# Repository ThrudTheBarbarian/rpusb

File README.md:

# rpusb
USB hub connecting RP2040s

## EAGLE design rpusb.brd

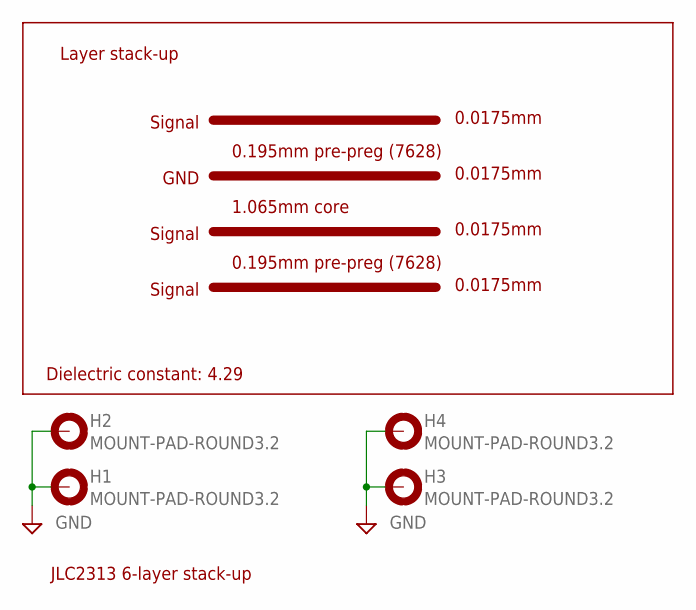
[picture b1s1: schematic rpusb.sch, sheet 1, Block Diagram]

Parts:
H1, H2, H3, H4: MOUNT-PAD-ROUND3.2; 3,2-PAD

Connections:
GND: H1.B3,2, H2.B3,2, H3.B3,2, H4.B3,2; also elsewhere on the board

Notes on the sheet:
JLC2313 6-layer stack-up
0.0175mm
Layer stack-up
Dielectric constant: 4.29
Signal
GND
0.195mm pre-preg (7628)
1.065mm core

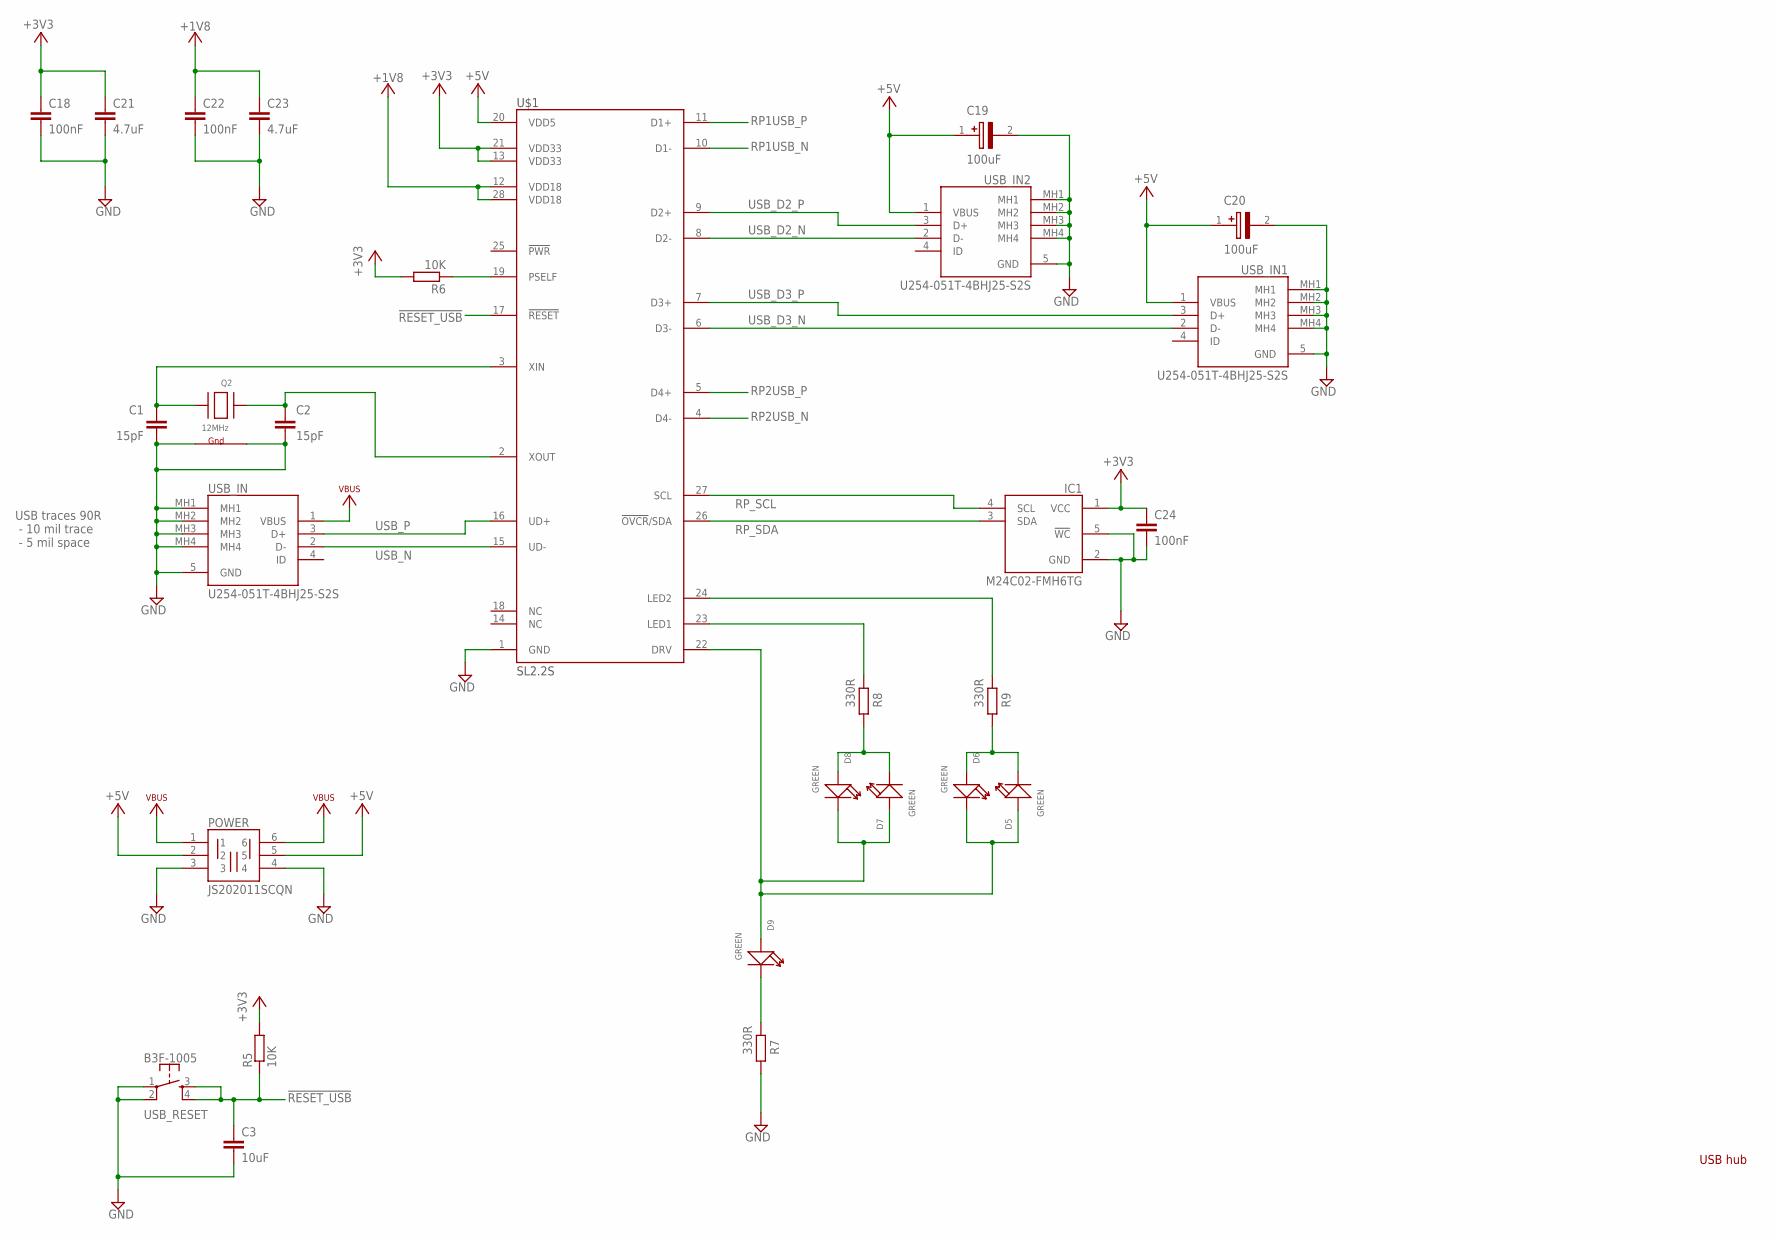
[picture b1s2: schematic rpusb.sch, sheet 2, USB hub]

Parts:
C1, C2: 15pF; C0201
C3: 10uF; C0402
C18, C22, C24: 100nF; C0201
C19, C20: 100uF; CAPAE530X550N
C21, C23: 4.7uF; C0402
D5, D6, D7, D8, D9: GREEN; LED-0603
IC1: M24C02-FMH6TG; M24C32FMH6TG
POWER: JS202011SCQN
Q2: 12MHz; NX3225
R5, R6: 10K; R0201
R7, R8, R9: 330R; R0201
U$1: SL2.2S; SSOP28-0.635
USB_IN, USB_IN1, USB_IN2: U254-051T-4BHJ25-S2S; U254051T4BHJ25S2S
USB_RESET: B3F-1005; TACTILE-PTH

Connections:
!RESET_USB!: C3.1, R5.1, U$1.17 (!RESET!), USB_RESET.3, USB_RESET.4
+1V8: C22.1, C23.1, U$1.12 (VDD18), U$1.28 (VDD18)
+3V3: C18.1, C21.1, C24.1, IC1.1 (VCC), R5.2, R6.2, U$1.13 (VDD33), U$1.21 (VDD33)
+5V: C19.1 (+), C20.1 (+), POWER.2, POWER.5, U$1.20 (VDD5), USB_IN1.1 (VBUS), USB_IN2.1 (VBUS); also elsewhere on the board
GND: C1.2, C2.2, C3.2, C18.2, C19.2 (-), C20.2 (-), C21.2, C22.2, C23.2, C24.2, IC1.2 (GND), IC1.5 (!WC), POWER.3, POWER.4, Q2.2 (G2), Q2.4 (G1), R7.1, U$1.1 (GND), USB_IN.5 (GND), USB_IN.MH1, USB_IN.MH2, USB_IN.MH3, USB_IN.MH4, USB_IN1.5 (GND), USB_IN1.MH1, USB_IN1.MH2, USB_IN1.MH3, USB_IN1.MH4, USB_IN2.5 (GND), USB_IN2.MH1, USB_IN2.MH2, USB_IN2.MH3, USB_IN2.MH4, USB_RESET.1, USB_RESET.2; also elsewhere on the board
unnamed: D9.-, R7.2
unnamed: C2.1, Q2.3 (X2), U$1.2 (XOUT)
unnamed: R6.1, U$1.19 (PSELF)
unnamed: C1.1, Q2.1 (X1), U$1.3 (XIN)
unnamed: R8.2, U$1.23 (LED1)
unnamed: D7.-, D8.+, R8.1
unnamed: D5.+, D6.-, D7.+, D8.-, D9.+, U$1.22 (DRV)
unnamed: R9.2, U$1.24 (LED2)
unnamed: D5.-, D6.+, R9.1
RP1USB_N: U$1.10 (D1-); also elsewhere on the board
RP1USB_P: U$1.11 (D1+); also elsewhere on the board
RP2USB_N: U$1.4 (D4-); also elsewhere on the board
RP2USB_P: U$1.5 (D4+); also elsewhere on the board
RP_SCL: IC1.4 (SCL), U$1.27 (SCL); also elsewhere on the board
RP_SDA: IC1.3 (SDA), U$1.26 (!OVCR!/SDA); also elsewhere on the board
USB_D2_N: U$1.8 (D2-), USB_IN2.2 (D-)
USB_D2_P: U$1.9 (D2+), USB_IN2.3 (D+)
USB_D3_N: U$1.6 (D3-), USB_IN1.2 (D-)
USB_D3_P: U$1.7 (D3+), USB_IN1.3 (D+)
USB_N: U$1.15 (UD-), USB_IN.2 (D-)
USB_P: U$1.16 (UD+), USB_IN.3 (D+)
VBUS: POWER.1, POWER.6, USB_IN.1 (VBUS); also elsewhere on the board

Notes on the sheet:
USB hub
USB traces 90R - 10 mil trace - 5 mil space

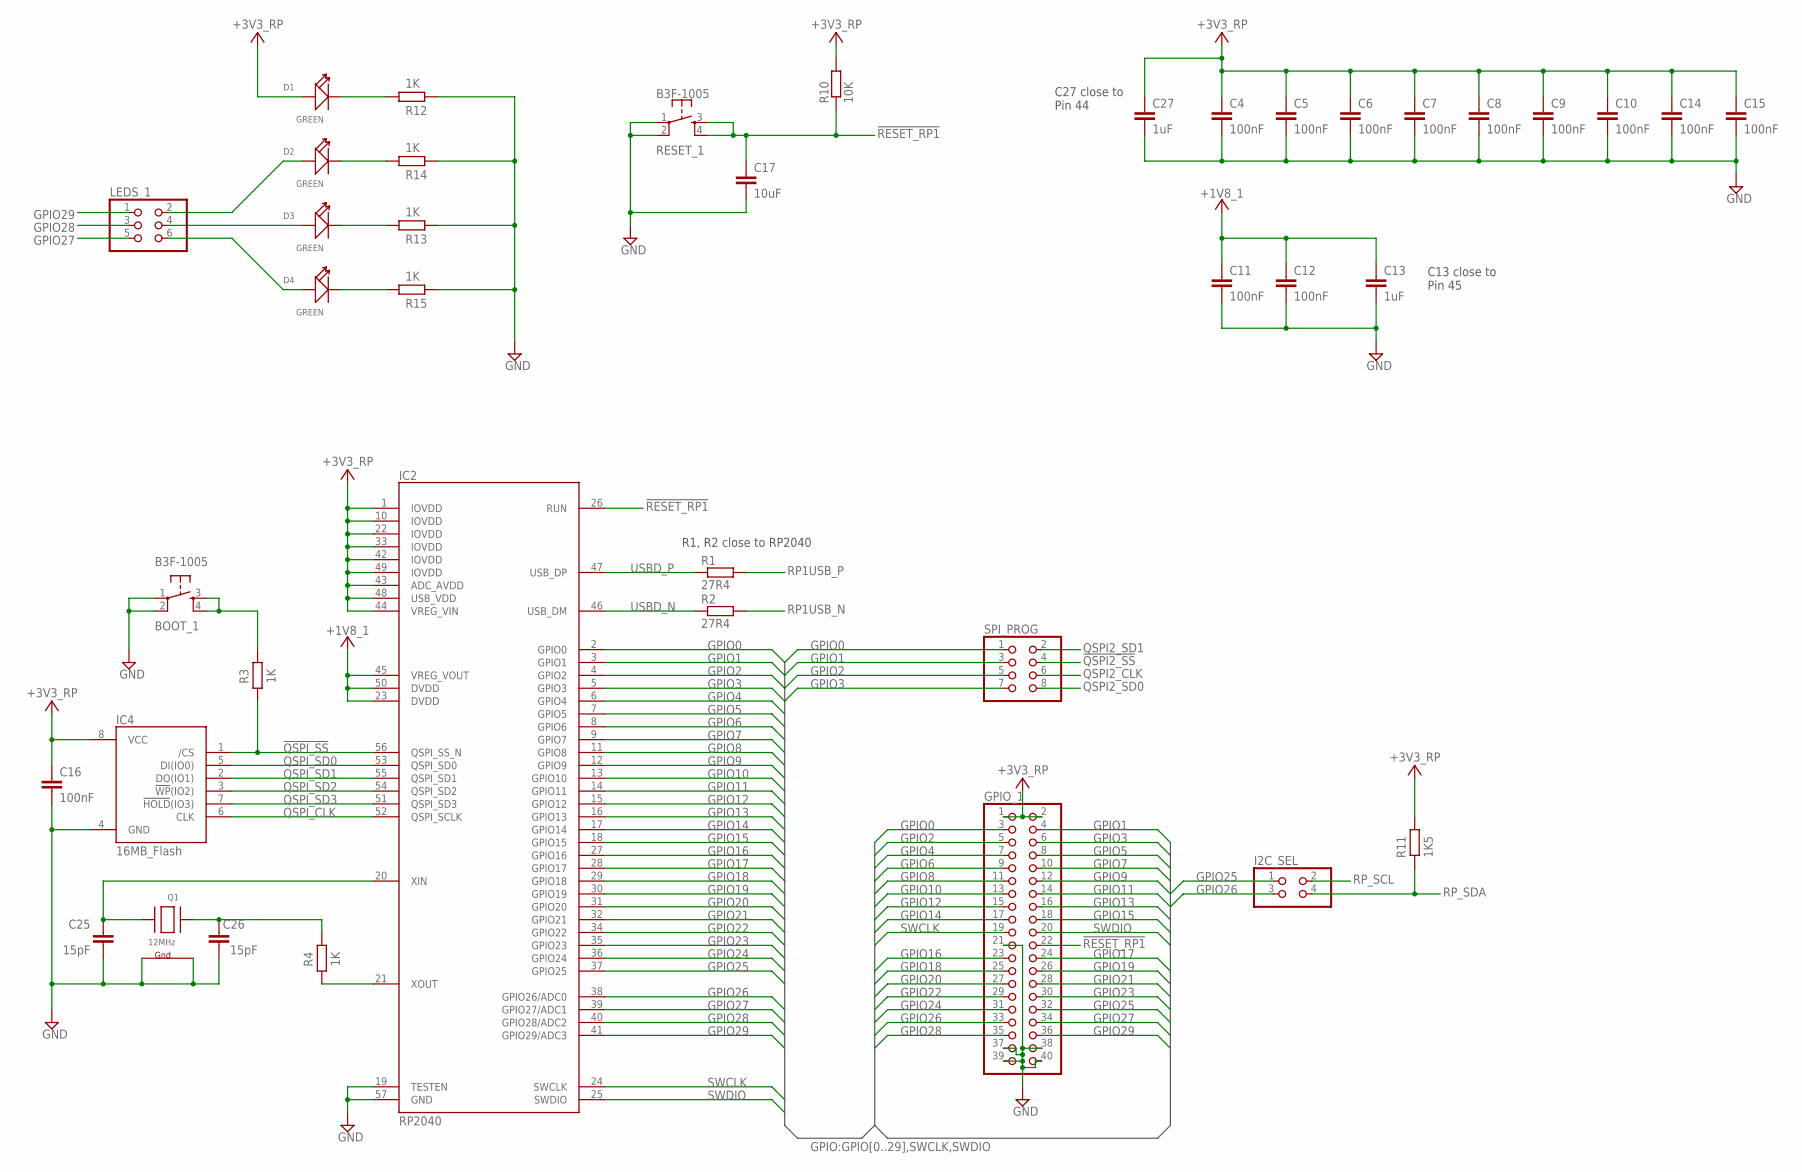
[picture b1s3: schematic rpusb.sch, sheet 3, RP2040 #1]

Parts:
BOOT_1: B3F-1005; TACTILE-PTH
C4, C5, C6, C7, C8, C9, C10, C11, C12, C14, C15, C16: 100nF; C0201
C13, C27: 1uF; C0201
C17: 10uF; C0402
C25, C26: 15pF; C0201
D1, D2, D3, D4: GREEN; LED-0603
GPIO_1: PINHD-2X20; 2X20
I2C_SEL: PINHD-2X2; 2X02
IC2: RP2040; QFN40P700X700X90-57N
IC4: 16MB_Flash; SOIC127P790X216-8N
LEDS_1: PINHD-2X3; 2X03
Q1: 12MHz; NX3225
R1, R2: 27R4; R0201
R3, R4, R12, R13, R14, R15: 1K; R0201
R10: 10K; R0201
R11: 1K5; R0201
RESET_1: B3F-1005; TACTILE-PTH
SPI_PROG: PINHD-2X4; 2X04

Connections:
!QSPI2_SS!: SPI_PROG.4; also elsewhere on the board
!QSPI_SS!: IC2.56 (QSPI_SS_N), IC4.1 (/CS), R3.2
!RESET_RP1!: C17.1, GPIO_1.22, IC2.26 (RUN), R10.1, RESET_1.3, RESET_1.4
+1V8_1: C11.1, C12.1, C13.1, IC2.23 (DVDD), IC2.45 (VREG_VOUT), IC2.50 (DVDD)
+3V3_RP: C4.1, C5.1, C6.1, C7.1, C8.1, C9.1, C10.1, C14.1, C15.1, C16.1, C27.1, D1.+, GPIO_1.1, GPIO_1.2, IC2.1 (IOVDD), IC2.10 (IOVDD), IC2.22 (IOVDD), IC2.33 (IOVDD), IC2.42 (IOVDD), IC2.43 (ADC_AVDD), IC2.44 (VREG_VIN), IC2.48 (USB_VDD), IC2.49 (IOVDD), IC4.8 (VCC), R10.2, R11.1; also elsewhere on the board
GND: BOOT_1.1, BOOT_1.2, C4.2, C5.2, C6.2, C7.2, C8.2, C9.2, C10.2, C11.2, C12.2, C13.2, C14.2, C15.2, C16.2, C17.2, C25.2, C26.2, C27.2, GPIO_1.21, GPIO_1.37, GPIO_1.38, GPIO_1.39, GPIO_1.40, IC2.19 (TESTEN), IC2.57 (GND), IC4.4 (GND), Q1.2 (G2), Q1.4 (G1), R12.2, R13.2, R14.2, R15.2, RESET_1.1, RESET_1.2; also elsewhere on the board
GPIO0: GPIO_1.3, IC2.2 (GPIO0), SPI_PROG.1
GPIO1: GPIO_1.4, IC2.3 (GPIO1), SPI_PROG.3
GPIO2: GPIO_1.5, IC2.4 (GPIO2), SPI_PROG.5
GPIO3: GPIO_1.6, IC2.5 (GPIO3), SPI_PROG.7
GPIO4: GPIO_1.7, IC2.6 (GPIO4)
GPIO5: GPIO_1.8, IC2.7 (GPIO5)
GPIO6: GPIO_1.9, IC2.8 (GPIO6)
GPIO7: GPIO_1.10, IC2.9 (GPIO7)
GPIO8: GPIO_1.11, IC2.11 (GPIO8)
GPIO9: GPIO_1.12, IC2.12 (GPIO9)
GPIO10: GPIO_1.13, IC2.13 (GPIO10)
GPIO11: GPIO_1.14, IC2.14 (GPIO11)
GPIO12: GPIO_1.15, IC2.15 (GPIO12)
GPIO13: GPIO_1.16, IC2.16 (GPIO13)
GPIO14: GPIO_1.17, IC2.17 (GPIO14)
GPIO15: GPIO_1.18, IC2.18 (GPIO15)
GPIO16: GPIO_1.23, IC2.27 (GPIO16)
GPIO17: GPIO_1.24, IC2.28 (GPIO17)
GPIO18: GPIO_1.25, IC2.29 (GPIO18)
GPIO19: GPIO_1.26, IC2.30 (GPIO19)
GPIO20: GPIO_1.27, IC2.31 (GPIO20)
GPIO21: GPIO_1.28, IC2.32 (GPIO21)
GPIO22: GPIO_1.29, IC2.34 (GPIO22)
GPIO23: GPIO_1.30, IC2.35 (GPIO23)
GPIO24: GPIO_1.31, IC2.36 (GPIO24)
GPIO25: GPIO_1.32, I2C_SEL.1, IC2.37 (GPIO25)
GPIO26: GPIO_1.33, I2C_SEL.3, IC2.38 (GPIO26/ADC0)
GPIO27: GPIO_1.34, IC2.39 (GPIO27/ADC1), LEDS_1.5
GPIO28: GPIO_1.35, IC2.40 (GPIO28/ADC2), LEDS_1.3
GPIO29: GPIO_1.36, IC2.41 (GPIO29/ADC3), LEDS_1.1
unnamed: D1.-, R12.1
unnamed: D2.-, R14.1
unnamed: BOOT_1.3, BOOT_1.4, R3.1
unnamed: D3.-, R13.1
unnamed: IC2.21 (XOUT), R4.2
unnamed: D4.-, R15.1
unnamed: D2.+, LEDS_1.2
unnamed: D3.+, LEDS_1.4
unnamed: D4.+, LEDS_1.6
unnamed: C26.1, Q1.3 (X2), R4.1
unnamed: C25.1, IC2.20 (XIN), Q1.1 (X1)
QSPI2_CLK: SPI_PROG.6; also elsewhere on the board
QSPI2_SD0: SPI_PROG.8; also elsewhere on the board
QSPI2_SD1: SPI_PROG.2; also elsewhere on the board
QSPI_CLK: IC2.52 (QSPI_SCLK), IC4.6 (CLK)
QSPI_SD0: IC2.53 (QSPI_SD0), IC4.5 (DI(IO0))
QSPI_SD1: IC2.55 (QSPI_SD1), IC4.2 (DO(IO1))
QSPI_SD2: IC2.54 (QSPI_SD2), IC4.3 (!WP!(IO2))
QSPI_SD3: IC2.51 (QSPI_SD3), IC4.7 (!HOLD!(IO3))
RP1USB_N: R2.2; also elsewhere on the board
RP1USB_P: R1.2; also elsewhere on the board
RP_SCL: I2C_SEL.2; also elsewhere on the board
RP_SDA: I2C_SEL.4, R11.2; also elsewhere on the board
SWCLK: GPIO_1.19, IC2.24 (SWCLK)
SWDIO: GPIO_1.20, IC2.25 (SWDIO)
USBD_N: IC2.46 (USB_DM), R2.1
USBD_P: IC2.47 (USB_DP), R1.1

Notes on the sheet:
R1, R2 close to RP2040
C13 close to Pin 45
C27 close to Pin 44

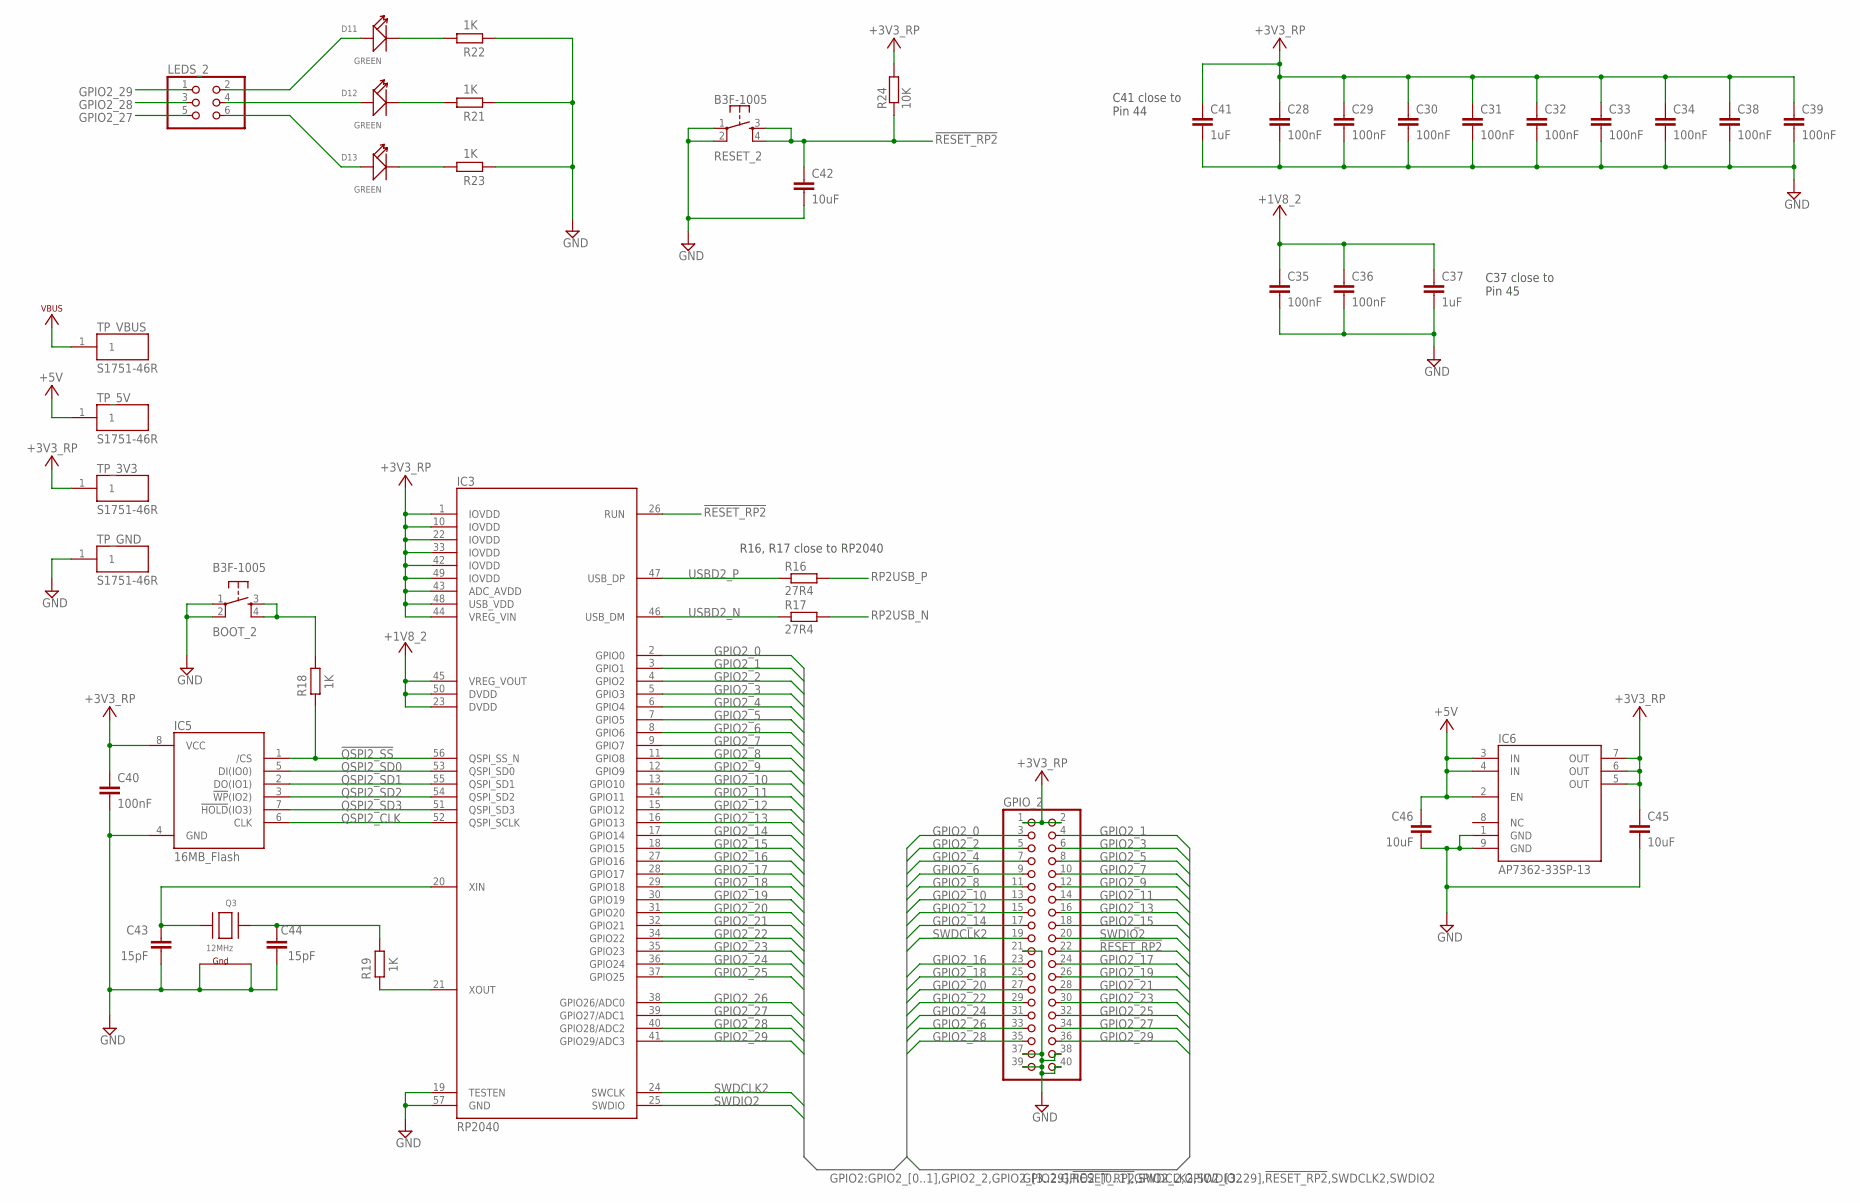
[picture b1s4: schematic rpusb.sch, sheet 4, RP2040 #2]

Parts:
BOOT_2: B3F-1005; TACTILE-PTH
C28, C29, C30, C31, C32, C33, C34, C35, C36, C38, C39, C40: 100nF; C0201
C37, C41: 1uF; C0201
C42, C45, C46: 10uF; C0402
C43, C44: 15pF; C0201
D11, D12, D13: GREEN; LED-0603
GPIO_2: PINHD-2X20; 2X20
IC3: RP2040; QFN40P700X700X90-57N
IC5: 16MB_Flash; SOIC127P790X216-8N
IC6: AP7362-33SP-13; SOIC127P600X163-9N
LEDS_2: PINHD-2X3; 2X03
Q3: 12MHz; NX3225
R16, R17: 27R4; R0201
R18, R19, R21, R22, R23: 1K; R0201
R24: 10K; R0201
RESET_2: B3F-1005; TACTILE-PTH
TP_3V3, TP_5V: S1751-46R; S175146R
TP_GND: S1751-46R; S175146R
TP_VBUS: S1751-46R; S175146R

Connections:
!QSPI2_SS!: IC3.56 (QSPI_SS_N), IC5.1 (/CS), R18.2; also elsewhere on the board
!RESET_RP2!: C42.1, GPIO_2.22, IC3.26 (RUN), R24.1, RESET_2.3, RESET_2.4
+1V8_2: C35.1, C36.1, C37.1, IC3.23 (DVDD), IC3.45 (VREG_VOUT), IC3.50 (DVDD)
+3V3_RP: C28.1, C29.1, C30.1, C31.1, C32.1, C33.1, C34.1, C38.1, C39.1, C40.1, C41.1, C45.1, GPIO_2.1, GPIO_2.2, IC3.1 (IOVDD), IC3.10 (IOVDD), IC3.22 (IOVDD), IC3.33 (IOVDD), IC3.42 (IOVDD), IC3.43 (ADC_AVDD), IC3.44 (VREG_VIN), IC3.48 (USB_VDD), IC3.49 (IOVDD), IC5.8 (VCC), IC6.5 (OUT), IC6.6 (OUT), IC6.7 (OUT), R24.2, TP_3V3.1; also elsewhere on the board
+5V: C46.1, IC6.2 (EN), IC6.3 (IN), IC6.4 (IN), TP_5V.1; also elsewhere on the board
GND: BOOT_2.1, BOOT_2.2, C28.2, C29.2, C30.2, C31.2, C32.2, C33.2, C34.2, C35.2, C36.2, C37.2, C38.2, C39.2, C40.2, C41.2, C42.2, C43.2, C44.2, C45.2, C46.2, GPIO_2.21, GPIO_2.37, GPIO_2.38, GPIO_2.39, GPIO_2.40, IC3.19 (TESTEN), IC3.57 (GND), IC5.4 (GND), IC6.1 (GND), IC6.9 (GND), Q3.2 (G2), Q3.4 (G1), R21.2, R22.2, R23.2, RESET_2.1, RESET_2.2, TP_GND.1; also elsewhere on the board
GPIO2_0: GPIO_2.3, IC3.2 (GPIO0)
GPIO2_1: GPIO_2.4, IC3.3 (GPIO1)
GPIO2_2: GPIO_2.5, IC3.4 (GPIO2)
GPIO2_3: GPIO_2.6, IC3.5 (GPIO3)
GPIO2_4: GPIO_2.7, IC3.6 (GPIO4)
GPIO2_5: GPIO_2.8, IC3.7 (GPIO5)
GPIO2_6: GPIO_2.9, IC3.8 (GPIO6)
GPIO2_7: GPIO_2.10, IC3.9 (GPIO7)
GPIO2_8: GPIO_2.11, IC3.11 (GPIO8)
GPIO2_9: GPIO_2.12, IC3.12 (GPIO9)
GPIO2_10: GPIO_2.13, IC3.13 (GPIO10)
GPIO2_11: GPIO_2.14, IC3.14 (GPIO11)
GPIO2_12: GPIO_2.15, IC3.15 (GPIO12)
GPIO2_13: GPIO_2.16, IC3.16 (GPIO13)
GPIO2_14: GPIO_2.17, IC3.17 (GPIO14)
GPIO2_15: GPIO_2.18, IC3.18 (GPIO15)
GPIO2_16: GPIO_2.23, IC3.27 (GPIO16)
GPIO2_17: GPIO_2.24, IC3.28 (GPIO17)
GPIO2_18: GPIO_2.25, IC3.29 (GPIO18)
GPIO2_19: GPIO_2.26, IC3.30 (GPIO19)
GPIO2_20: GPIO_2.27, IC3.31 (GPIO20)
GPIO2_21: GPIO_2.28, IC3.32 (GPIO21)
GPIO2_22: GPIO_2.29, IC3.34 (GPIO22)
GPIO2_23: GPIO_2.30, IC3.35 (GPIO23)
GPIO2_24: GPIO_2.31, IC3.36 (GPIO24)
GPIO2_25: GPIO_2.32, IC3.37 (GPIO25)
GPIO2_26: GPIO_2.33, IC3.38 (GPIO26/ADC0)
GPIO2_27: GPIO_2.34, IC3.39 (GPIO27/ADC1), LEDS_2.5
GPIO2_28: GPIO_2.35, IC3.40 (GPIO28/ADC2), LEDS_2.3
GPIO2_29: GPIO_2.36, IC3.41 (GPIO29/ADC3), LEDS_2.1
unnamed: BOOT_2.3, BOOT_2.4, R18.1
unnamed: IC3.21 (XOUT), R19.2
unnamed: D11.-, R22.1
unnamed: D12.-, R21.1
unnamed: D13.-, R23.1
unnamed: D11.+, LEDS_2.2
unnamed: D12.+, LEDS_2.4
unnamed: D13.+, LEDS_2.6
unnamed: C44.1, Q3.3 (X2), R19.1
unnamed: C43.1, IC3.20 (XIN), Q3.1 (X1)
QSPI2_CLK: IC3.52 (QSPI_SCLK), IC5.6 (CLK); also elsewhere on the board
QSPI2_SD0: IC3.53 (QSPI_SD0), IC5.5 (DI(IO0)); also elsewhere on the board
QSPI2_SD1: IC3.55 (QSPI_SD1), IC5.2 (DO(IO1)); also elsewhere on the board
QSPI2_SD2: IC3.54 (QSPI_SD2), IC5.3 (!WP!(IO2))
QSPI2_SD3: IC3.51 (QSPI_SD3), IC5.7 (!HOLD!(IO3))
RP2USB_N: R17.2; also elsewhere on the board
RP2USB_P: R16.2; also elsewhere on the board
SWDCLK2: GPIO_2.19, IC3.24 (SWCLK)
SWDIO2: GPIO_2.20, IC3.25 (SWDIO)
USBD2_N: IC3.46 (USB_DM), R17.1
USBD2_P: IC3.47 (USB_DP), R16.1
VBUS: TP_VBUS.1; also elsewhere on the board

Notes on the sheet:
R16, R17 close to RP2040
C37 close to Pin 45
C41 close to Pin 44

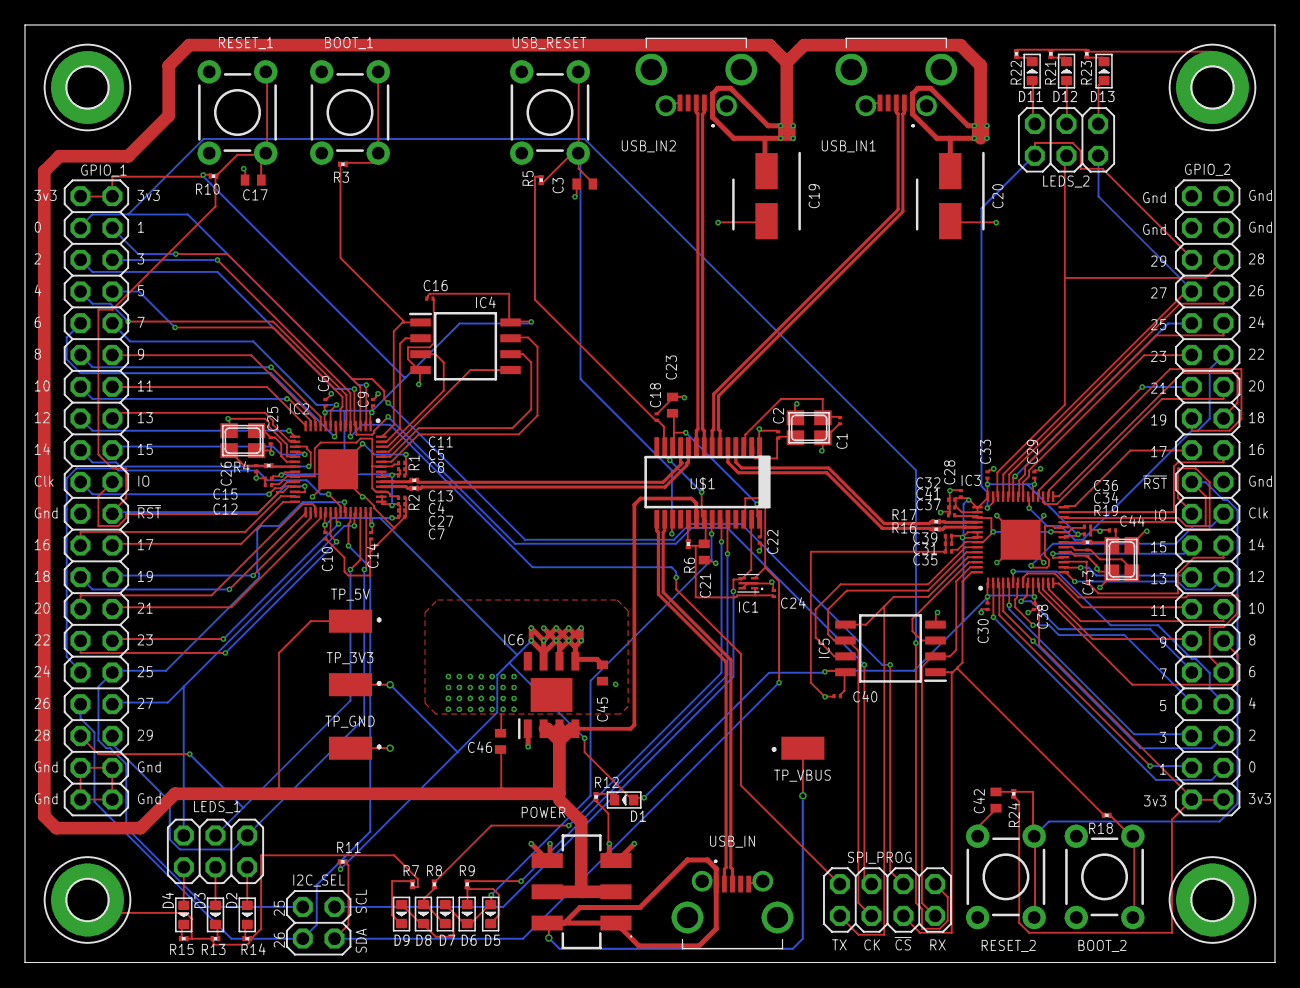
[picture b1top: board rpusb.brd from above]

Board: 4 copper layers, 100.0 x 75.0 mm, 114 parts (0 on the bottom side), 133 nets.

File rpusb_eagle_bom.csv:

"Qty";"Value";"Device";"Package";"Parts";"Description";"ARROW_PART_NUMBER";"ARROW_PRICE-STOCK";"DESCRIPTION";"HEIGHT";"MANUFACTURER_NAME";"MANUFACTURER_PART_NUMBER";"MOUSER_PART_NUMBER";"MOUSER_PRICE-STOCK";"MPN";"POPULARITY";"SPICEPREFIX";"USE";"VALUE";
"1";"";"PINHD-2X2";"2X02";"I2C_SEL";"PIN HEADER";"";"";"";"";"";"";"";"";"";"0";"";"";"";
"2";"";"PINHD-2X20";"2X20";"GPIO_1, GPIO_2";"PIN HEADER";"";"";"";"";"";"";"";"";"";"12";"";"";"";
"2";"";"PINHD-2X3";"2X03";"LEDS_1, LEDS_2";"PIN HEADER";"";"";"";"";"";"";"";"";"";"62";"";"";"";
"3";"";"XTAL-4-3225";"NX3225";"Q1, Q2, Q3";"Classic 4-pin 3.2 x 2.5mm crystal";"";"";"";"";"";"";"";"";"";"";"";"RH100-12.000-9-1015-TR-NS1";"";
"27";"100nF";"C-EUC0201";"C0201";"C4, C5, C6, C7, C8, C9, C10, C11, C12, C14, C15, C16, C18, C22, C24, C28, C29, C30, C31, C32, C33, C34, C35, C36, C38, C39, C40";"CAPACITOR, European symbol";"";"";"";"";"";"";"";"";"";"0";"C";"0201X104M160CT";"";
"2";"100uF";"865080142007";"CAPAE530X550N";"C19, C20";"Wurth Elektronik 100uF 25 V dc Aluminium Electrolytic Capacitor, WCAP-ASLI Series 2000h 5 (Dia.) x 5.35mm";"";"";"Wurth Elektronik 100uF 25 V dc Aluminium Electrolytic Capacitor, WCAP-ASLI Series 2000h 5 (Dia.) x 5.35mm";"5.5mm";"Wurth Elektronik";"865080142007";"710-865080142007";"https://www.mouser.co.uk/ProductDetail/Wurth-Elektronik/8650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";"";"";"";" 865080142007";"";
"4";"10K";"R-EU_R0201";"R0201";"R5, R6, R10, R24";"RESISTOR, European symbol";"";"";"";"";"";"";"";"";"";"0";"R";"CR0201-JW-103GLF";"";
"5";"10uF";"C-EUC0402";"C0402";"C3, C17, C42, C45, C46";"CAPACITOR, European symbol";"";"";"";"";"";"";"";"";"";"18";"C";"CL05A106MP5NUNC";"";
"6";"15pF";"C-EUC0201";"C0201";"C1, C2, C25, C26, C43, C44";"CAPACITOR, European symbol";"";"";"";"";"";"";"";"";"";"0";"C";"0201N150J500CT";"";
"2";"16MB_Flash";"W25Q128JVSIM_TR";"SOIC127P790X216-8N";"IC4, IC5";"3V 128M-BIT SERIAL FLASH MEMORY WITH DUAL/QUAD SPI & QPI & DTR";"W25Q128JVSIM TR";"https://www.arrow.com/en/products/w25q128jvsimtr/winbond-ele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";"3V 128M-BIT SERIAL FLASH MEMORY WITH DUAL/QUAD SPI & QPI & DTR";"2.16mm";"Winbond";"W25Q128JVSIM TR";"454-W25Q128JVSIMTR";"https://www.mouser.co.uk/ProductDetail/Winbond/W25Q128JVSIM-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";"";"";"";"W25Q128JVSIM";"";
"11";"1K";"R-EU_R0201";"R0201";"R3, R4, R12, R13, R14, R15, R18, R19, R21, R22, R23";"RESISTOR, European symbol";"";"";"";"";"";"";"";"";"";"0";"R";"RC0201FR-071KL";"";
"1";"1K5";"R-EU_R0201";"R0201";"R11";"RESISTOR, European symbol";"";"";"";"";"";"";"";"";"";"0";"R";"RMCF0201FT1K50";"";
"4";"1uF";"C-EUC0201";"C0201";"C13, C27, C37, C41";"CAPACITOR, European symbol";"";"";"";"";"";"";"";"";"";"0";"C";"0201B102K250CT";"";
"4";"27R4";"R-EU_R0201";"R0201";"R1, R2, R16, R17";"RESISTOR, European symbol";"";"";"";"";"";"";"";"";"";"0";"R";"RC0201FR-0727R4L";"";
"3";"330R";"R-EU_R0201";"R0201";"R7, R8, R9";"RESISTOR, European symbol";"";"";"";"";"";"";"";"";"";"0";"R";"RMCF0201FT330R";"";
"2";"4.7uF";"C-EUC0402";"C0402";"C21, C23";"CAPACITOR, European symbol";"";"";"";"";"";"";"";"";"";"18";"C";"CL05A475MP5NRNC";"";
"1";"AP7362-33SP-13";"AP7362-33SP-13";"SOIC127P600X163-9N";"IC6";"LDO Voltage Regulators LDO CMOS HiCurr SO-8 1.5A LowQ Adj 190mV";"AP7362-33SP-13";"https://www.arrow.com/en/products/ap7362-33sp-13/diodes-inco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";"LDO Voltage Regulators LDO CMOS HiCurr SO-8 1.5A LowQ Adj 190mV";"1.63mm";"Diodes Inc.";"AP7362-33SP-13";"621-AP7362-33SP-13";"https://www.mouser.co.uk/ProductDetail/Diodes-Incorporated/A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";"";"";"";"AP7362-33SP-13";"";
"5";"B3F-1005";"TAC_SWITCHPTH";"TACTILE-PTH";"BOOT_1, BOOT_2, RESET_1, RESET_2, USB_RESET";"Momentary Switch";"";"";"";"";"";"";"";"";"";"";"";"B3F-1005";"";
"12";"GREEN";"SMD-LED-CLEAR-BLUE(0603)";"LED-0603";"D1, D2, D3, D4, D5, D6, D7, D8, D9, D11, D12, D13";"304090045";"";"";"";"";"";"";"";"";"19-217-BHC-ZL1M2RY-3T";"";"";"B1931NG--20D001114U1930";"BLUE-0603";
"1";"JS202011SCQN";"JS202011SCQN";"JS202011SCQN";"POWER";"Sub miniature slide switches";"JS202011SCQN";"https://www.arrow.com/en/products/js202011scqn/ck?region=nac";"Sub miniature slide switches";"5.5mm";"C & K COMPONENTS";"JS202011SCQN";"611-JS202011SCQN";"https://www.mouser.co.uk/ProductDetail/CK/JS202011SCQN?qs=Lg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";"";"";"";"JS202011SCQN";"";
"1";"M24C02-FMH6TG";"M24C02-FMH6TG";"M24C32FMH6TG";"IC1";"STMICROELECTRONICS - M24C02-FMH6TG - EEPROM, 2 Kbit, 256 x 8bit, Serial I2C (2-Wire), 400 kHz, DFN, 5 Pins";"M24C02-FMH6TG";"https://www.arrow.com/en/products/m24c02-fmh6tg/stmicroelect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";"STMICROELECTRONICS - M24C02-FMH6TG - EEPROM, 2 Kbit, 256 x 8bit, Serial I2C (2-Wire), 400 kHz, DFN, 5 Pins";"0.6mm";"STMicroelectronics";"M24C02-FMH6TG";"511-M24C02-FMH6TG";"https://www.mouser.co.uk/ProductDetail/STMicroelectronics/M2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";"";"";"";"M24C02-FMH6TG";"";
"4";"MOUNT-PAD-ROUND3.2";"MOUNT-PAD-ROUND3.2";"3,2-PAD";"H1, H2, H3, H4";"MOUNTING PAD, round";"";"";"";"";"";"";"";"";"";"4";"";"";"";
"3";"Micro-B";"MCR-B-S-RA-SMT-CS14-T_R";"MCRBSRASMTCS14TR";"J2, J3, USB_IN";"USB - micro B Receptacle Connector 5 Position Surface Mount, Right Angle";"MCR-B-S-RA-SMT-CS14-T/R";"https://www.arrow.com/en/products/mcr-b-s-ra-smt-cs14-tr/ada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";"USB - micro B Receptacle Connector 5 Position Surface Mount, Right Angle";"3.1mm";"Adam Tech";"MCR-B-S-RA-SMT-CS14-T/R";"";"";"";"";"";"MCR-B-S-RA-SMT-CS14-T_R";"";
"2";"RP2040";"RP2040";"QFN40P700X700X90-57N";"IC2, IC3";"Microcontroller in QFN Package";"";"";"Microcontroller in QFN Package";"0.9mm";"RASPBERRY-PI";"RP2040";"";"";"";"";"";"SC0914(13)";"";
"1";"SL2.2S";"SL2.2S";"SSOP28-0.635";"U$1";"SL2.2s High, Full and Low speed USB2 hub";"";"";"";"";"";"";"";"";"";"";"";"SL2.2s";"";

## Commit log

2022-04-10 Initial circuit design
2022-04-11 First stab at routing the board - set up for JCLPCB
2022-04-11 Better routing
2022-04-11 Ready to order from NextPCB
2022-04-12 As submitted to NextPCB

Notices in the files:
parts and their libraries:
SparkFun: Licensing: CC v3.0 Share-Alike You are welcome to use this library for commercial purposes.
